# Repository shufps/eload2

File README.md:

> ⚠️ **Disclaimer / Status**
>
> This project is provided **AS IS**, **without any warranty** and **without any kind of support**.
> Use at your own risk — this is **high-current / high-power** hardware and can damage equipment or cause injury if used incorrectly.

# eload2 (Load v2)

A compact, over-engineered **multi-channel electronic load** for **low-voltage / high-current** testing — built because nothing affordable exists that does *0–1.5V @ ~100A* properly.

No display. Control via **USB** from a PC (Python), firmware on **STM32**.

## Why this exists

I needed a tool to:
- test **buck converters / VRMs** in the **0–1.5V** range at serious currents
- still be usable as a “normal” load at **12V** (e.g. for power supplies / battery projects)
- be stable, repeatable and boring (in the good sense)

Commercial options in this niche are either impractical or unreasonably expensive — so I built it.

## Highlights

- **4 independent channels**
- Designed for:
  - **0–1.5V** VRM / buck testing up to **~100A** total (depending on cooling & SOA)
  - **12V** testing (e.g. ~8–12A, depending on dissipation)
- Each channel has its own analog supply chain (low coupling, predictable behavior):
  - dedicated **9V LDO**
  - dedicated precision **reference** (REF3433)
  - dedicated **16-bit DAC**
  - dedicated **OPA2196** control loop
  - dedicated MOSFET “arm”
- MOSFETs: **BUK7S0R5-40HJ** (very low Rds(on), beefy SOA)
- Cooling: **SP3/TR4 CPU cooler** (tested in practice)
- High-current IO: **M4** power connections (aiming for ~80A per connector)
- PCB: **120 × 160 mm**, **4-layer**, 1oz/1oz
  (large copper, parallel layers, big via arrays; optional copper busbars)

## Status

- PCBs + stencil: ✅
- Parts: ✅ (BOM originally ~1.5 years old, most parts still available)
- Bring-up: ✅
- Verified load test: **12V @ 10A (120W) for ~15 min → ~55°C board temperature** (with the big cooler)

## Errata

- Current setting is a little bit off. For example 11.5A needs to be set for 10.0A current.

## Minimalistic Web UI

There is a minimalistic web UI.

It can be run using `streamlit`:
```bash
streamlit run eload_ui.py
```

## Documentation

https://www.mikrocontroller.net/topic/563073

## Repository structure (typical)

- `kicad/` – schematics, PCB, mechanical notes
- `firmware/` – STM32 firmware (Rust, Embassy)
- `python/` – PC tooling / scripts (Python)

## Quick start

### Firmware
- Build/flash using your usual STM32 + Rust toolchain.
- This project uses **Embassy** async tasks.

### Host control
- Connect the board via USB.
- Use the Python scripts to set:
  - per-channel DAC setpoints
  - PWM / fan / enable (depending on build)
  - read back telemetry (if enabled)

## Safety / Notes

This is a **high current** design.
- Use short, thick wiring for low-voltage/high-current tests.
- Treat every milliohm as a heater.
- Ensure solid cooling and stable mounting before sustained high power tests.
- If you don’t know what you’re doing: don’t connect this to expensive hardware.

## License

CERN-OHL-S: https://ohwr.org/cern_ohl_s_v2.pdf

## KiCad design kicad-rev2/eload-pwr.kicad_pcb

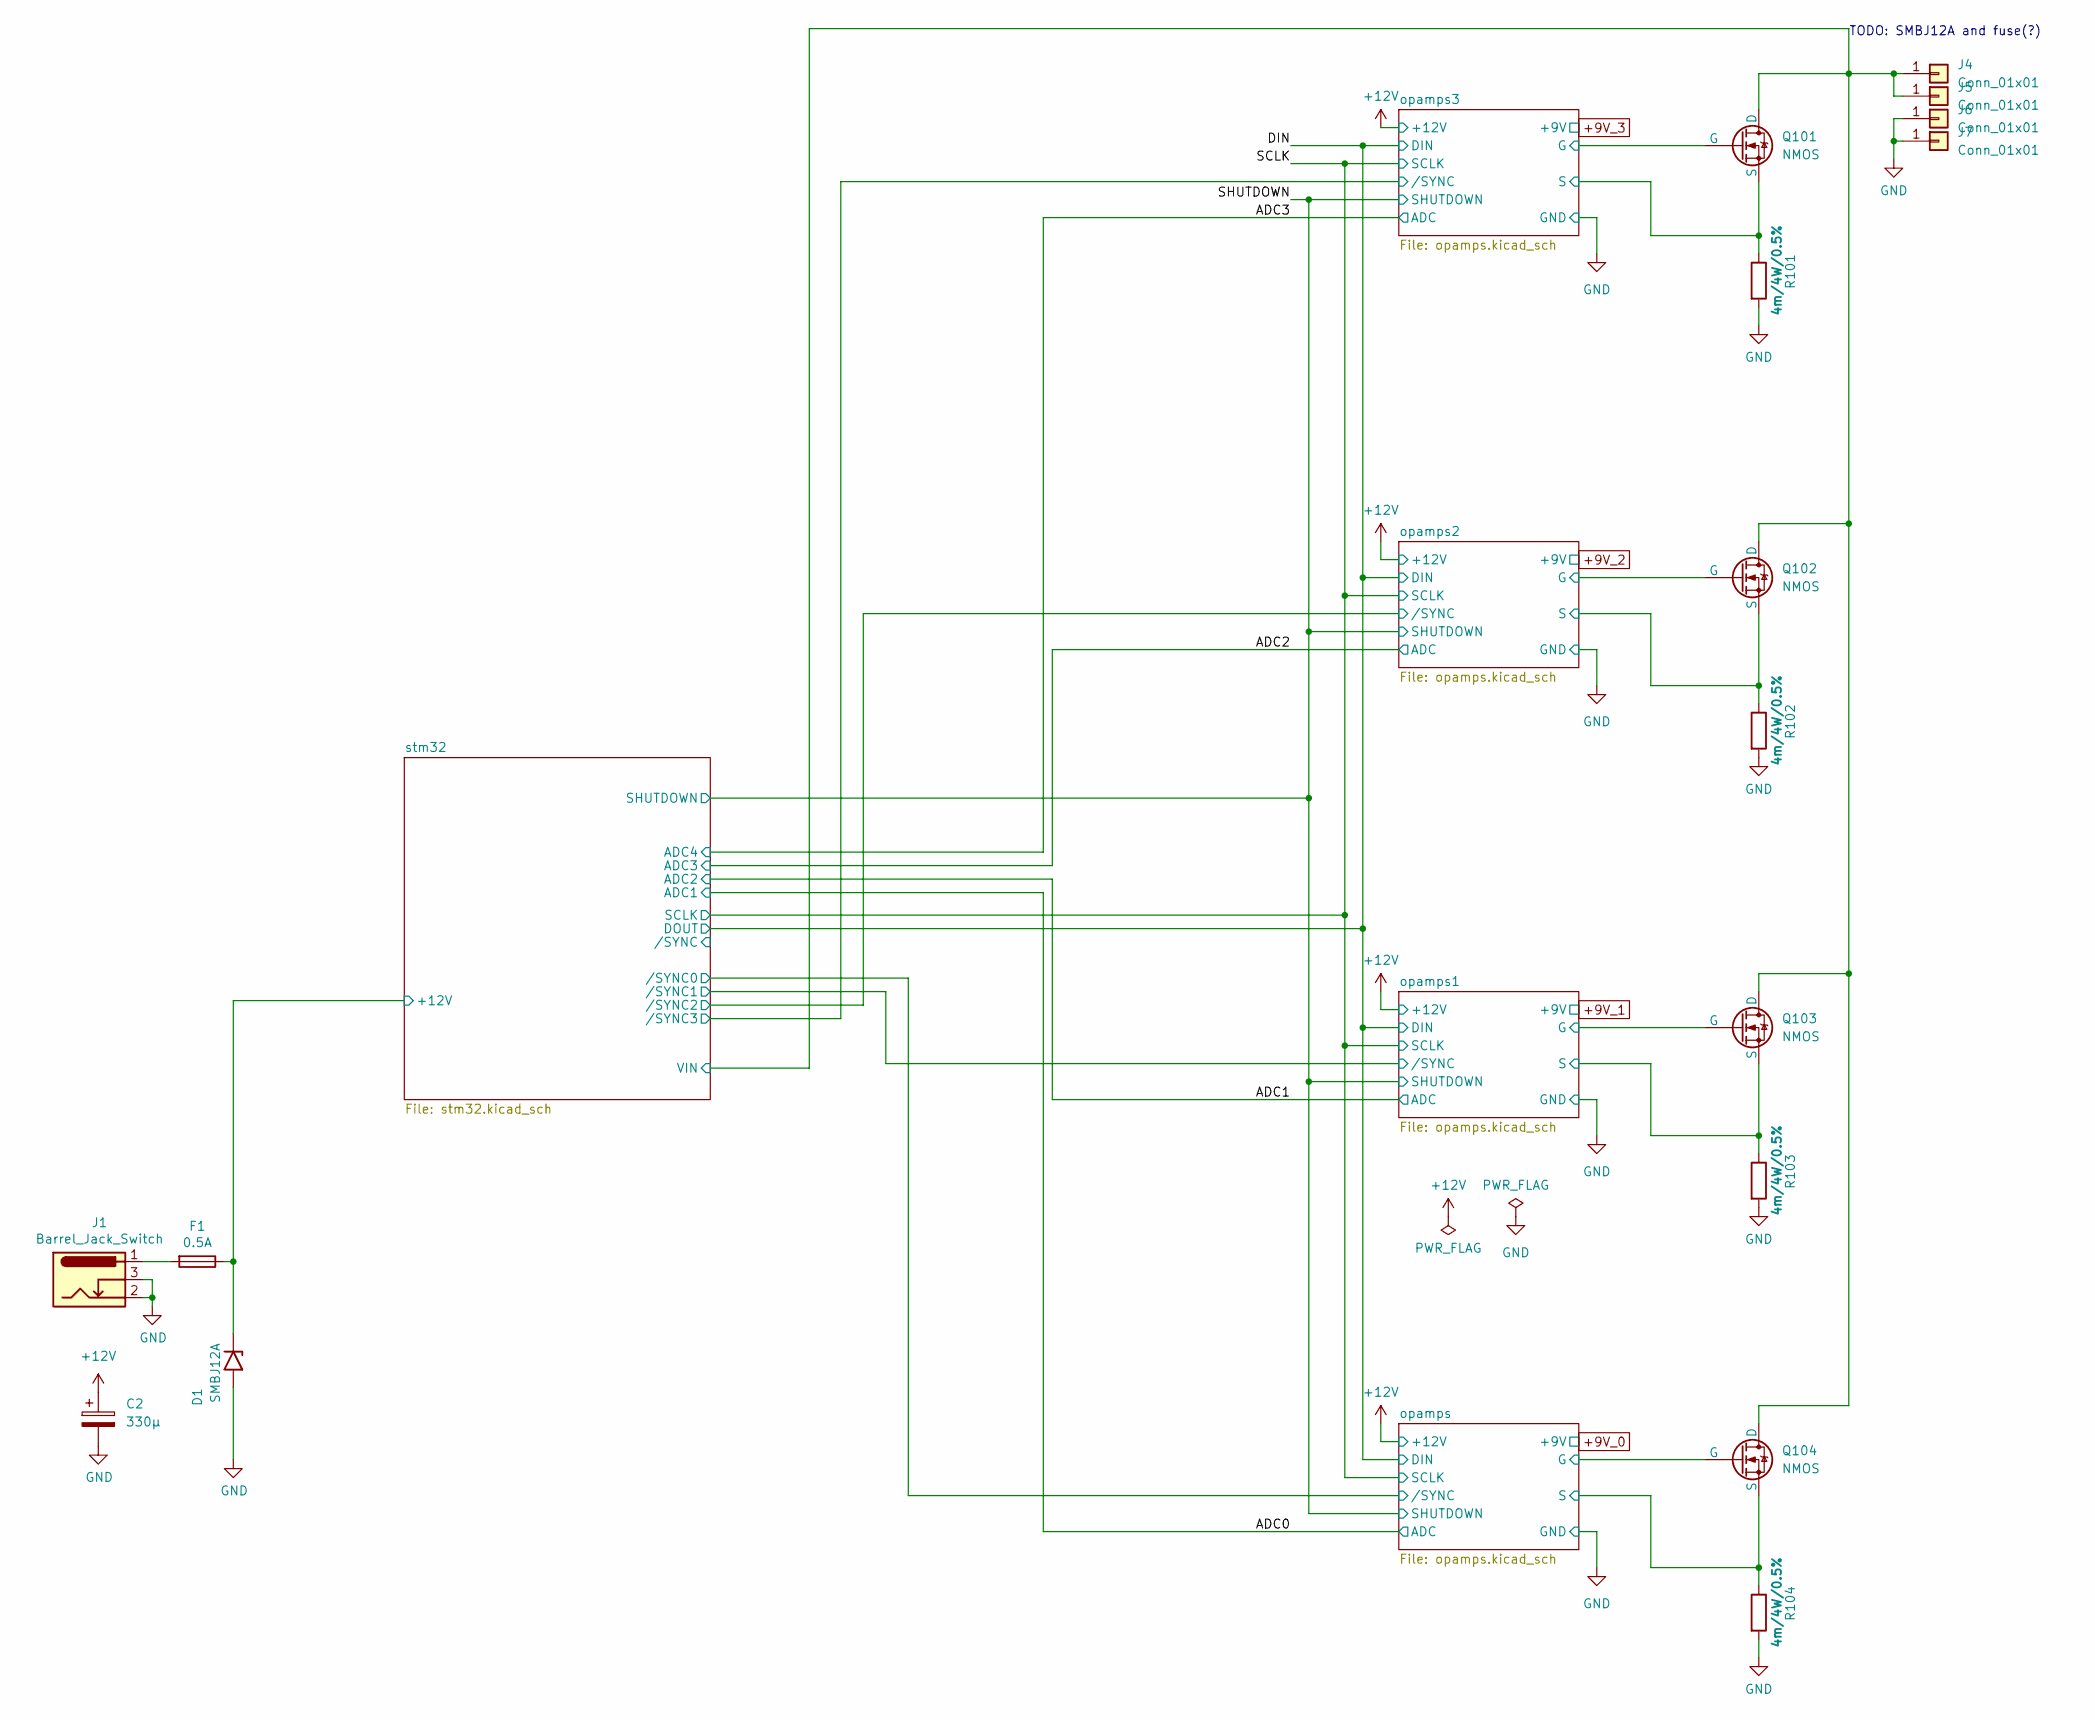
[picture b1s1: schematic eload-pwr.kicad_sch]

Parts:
C2: 330µ; CP_Elec_8x10
D1: SMBJ12A; D_SMB
F1: 0.5A; fuseholder_littlefuse_blok
J1: Barrel_Jack_Switch; BarrelJack_CUI_PJ-102AH_Horizontal
J4, J5, J6, J7: Conn_01x01; Wuerth_REDCUBE-THR_WP-THRBU_74650194_THR
Q101, Q102, Q103, Q104: NMOS; LFPAK88-SOT1235
R101, R102, R103, R104: 4m/4W/0.5%; R3920

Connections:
+12V: C2.1, D1.1 (A1), F1.1; also elsewhere on the board
/opamps1/G: Q103.G; also elsewhere on the board
/opamps1/S: Q103.S, R103.1; also elsewhere on the board
/opamps2/G: Q102.G; also elsewhere on the board
/opamps2/S: Q102.S, R102.1; also elsewhere on the board
/opamps3/G: Q101.G; also elsewhere on the board
/opamps3/S: Q101.S, R101.1; also elsewhere on the board
/opamps/G: Q104.G; also elsewhere on the board
/opamps/S: Q104.S, R104.1; also elsewhere on the board
/stm32/VIN: J4.1, J5.1, Q101.D, Q102.D, Q103.D, Q104.D; also elsewhere on the board
GND: C2.2, D1.2 (A2), J1.2, J1.3, J6.1, J7.1, R101.2, R102.2, R103.2, R104.2; also elsewhere on the board
unnamed: F1.2, J1.1

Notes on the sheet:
TODO: SMBJ12A and fuse(?)

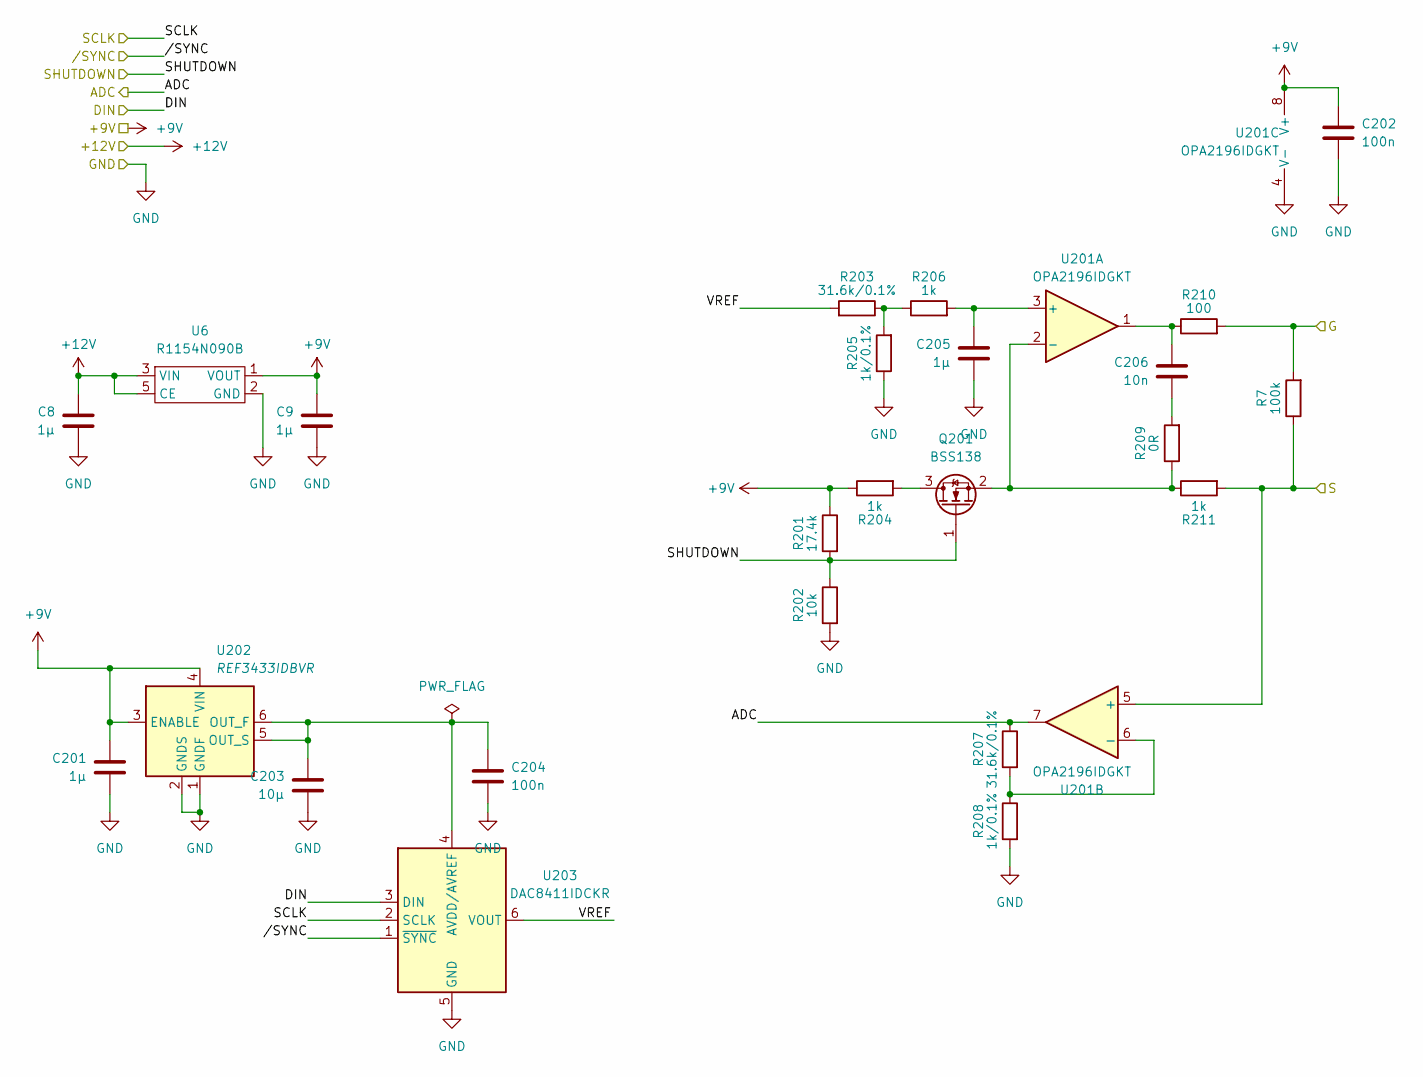
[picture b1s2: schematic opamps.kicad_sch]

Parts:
C8, C9, C201, C205: 1µ; C_0603_1608Metric
C202, C204: 100n; C_0603_1608Metric
C203: 10µ; C_0603_1608Metric
C206: 10n; C_0603_1608Metric
Q201: BSS138; SOT-23
R7: 100k; R_0603_1608Metric
R201: 17.4k; R_0603_1608Metric
R202: 10k; R_0603_1608Metric
R203, R207: 31.6k/0.1%; R_0603_1608Metric
R204, R206, R211: 1k; R_0603_1608Metric
R205, R208: 1k/0.1%; R_0603_1608Metric
R209: 0R; R_0603_1608Metric
R210: 100; R_0603_1608Metric
U6: R1154N090B; SOT-23-5
U201: OPA2196IDGKT; VSSOP-8_3.0x3.0mm_P0.65mm
U202: REF3433IDBVR; SOT-23-6
U203: DAC8411IDCKR; SOT-363_SC-70-6

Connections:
+9V_0: C9.1, C201.1, C202.1, R201.1, R204.1, U6.1 (VOUT), U201.8 (V+), U202.3 (ENABLE), U202.4 (VIN)
+12V: C8.1, U6.3 (VIN), U6.5 (CE); also elsewhere on the board
/ADC0: R207.1, U201.7; also elsewhere on the board
/DIN: U203.3 (DIN); also elsewhere on the board
/SCLK: U203.2 (SCLK); also elsewhere on the board
/SHUTDOWN: Q201.1 (G), R201.2, R202.1; also elsewhere on the board
/opamps/G: R7.2, R210.2; also elsewhere on the board
/opamps/S: R7.1, R211.2, U201.5 (+); also elsewhere on the board
/opamps/VREF: R203.2, U203.6 (VOUT)
/opamps//SYNC: U203.1 (~SYNC); also elsewhere on the board
GND: C8.2, C9.2, C201.2, C202.2, C203.2, C204.2, C205.2, R202.2, R205.1, R208.2, U6.2 (GND), U201.4 (V-), U202.1 (GNDF), U202.2 (GNDS), U203.5 (GND); also elsewhere on the board
unnamed: C206.1, R210.1, U201.1
unnamed: C206.2, R209.2
unnamed: Q201.3 (D), R204.2
unnamed: Q201.2 (S), R209.1, R211.1, U201.2 (-)
unnamed: R203.1, R205.2, R206.1
unnamed: C205.1, R206.2, U201.3 (+)
unnamed: R207.2, R208.1, U201.6 (-)
unnamed: C203.1, C204.1, U202.5 (OUT_S), U202.6 (OUT_F), U203.4 (AVDD/AVREF)

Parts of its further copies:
C12, C16, C17, C21, C22, C23, C301, C305, C401, C405, C501, C505: 1µ; C_0603_1608Metric
C302, C304, C402, C404, C502, C504: 100n; C_0603_1608Metric
C303, C403, C503: 10µ; C_0603_1608Metric
C306, C406, C506: 10n; C_0603_1608Metric
Q301, Q401, Q501: BSS138; SOT-23
R9, R10, R11: 100k; R_0603_1608Metric
R301, R401, R501: 17.4k; R_0603_1608Metric
R302, R402, R502: 10k; R_0603_1608Metric
R303, R307, R403, R407, R503, R507: 31.6k/0.1%; R_0603_1608Metric
R304, R306, R311, R404, R406, R411, R504, R506, R511: 1k; R_0603_1608Metric
R305, R308, R405, R408, R505, R508: 1k/0.1%; R_0603_1608Metric
R309, R409, R509: 0R; R_0603_1608Metric
R310, R410, R510: 100; R_0603_1608Metric
U7, U8, U9: R1154N090B; SOT-23-5
U301, U401, U501: OPA2196IDGKT; VSSOP-8_3.0x3.0mm_P0.65mm
U302, U402, U502: REF3433IDBVR; SOT-23-6
U303, U403, U503: DAC8411IDCKR; SOT-363_SC-70-6

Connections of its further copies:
+9V_1: C16.1, C301.1, C302.1, R301.1, R304.1, U7.1 (VOUT), U301.8 (V+), U302.3 (ENABLE), U302.4 (VIN)
+9V_2: C21.1, C401.1, C402.1, R401.1, R404.1, U8.1 (VOUT), U401.8 (V+), U402.3 (ENABLE), U402.4 (VIN)
+9V_3: C23.1, C501.1, C502.1, R501.1, R504.1, U9.1 (VOUT), U501.8 (V+), U502.3 (ENABLE), U502.4 (VIN)
+12V: C12.1, C17.1, C22.1, U7.3 (VIN), U7.5 (CE), U8.3 (VIN), U8.5 (CE), U9.3 (VIN), U9.5 (CE); also elsewhere on the board
/ADC1: R307.1, U301.7; also elsewhere on the board
/ADC2: R407.1, U401.7; also elsewhere on the board
/ADC3: R507.1, U501.7; also elsewhere on the board
/DIN: U303.3 (DIN), U403.3 (DIN), U503.3 (DIN); also elsewhere on the board
/SCLK: U303.2 (SCLK), U403.2 (SCLK), U503.2 (SCLK); also elsewhere on the board
/SHUTDOWN: Q301.1 (G), Q401.1 (G), Q501.1 (G), R301.2, R302.1, R401.2, R402.1, R501.2, R502.1; also elsewhere on the board
/opamps1/G: R9.2, R310.2; also elsewhere on the board
/opamps1/S: R9.1, R311.2, U301.5 (+); also elsewhere on the board
/opamps1/VREF: R303.2, U303.6 (VOUT)
/opamps1//SYNC: U303.1 (~SYNC); also elsewhere on the board
/opamps2/G: R10.2, R410.2; also elsewhere on the board
/opamps2/S: R10.1, R411.2, U401.5 (+); also elsewhere on the board
/opamps2/VREF: R403.2, U403.6 (VOUT)
/opamps2//SYNC: U403.1 (~SYNC); also elsewhere on the board
/opamps3/G: R11.2, R510.2; also elsewhere on the board
/opamps3/S: R11.1, R511.2, U501.5 (+); also elsewhere on the board
/opamps3/VREF: R503.2, U503.6 (VOUT)
/opamps3//SYNC: U503.1 (~SYNC); also elsewhere on the board
GND: C12.2, C16.2, C17.2, C21.2, C22.2, C23.2, C301.2, C302.2, C303.2, C304.2, C305.2, C401.2, C402.2, C403.2, C404.2, C405.2, C501.2, C502.2, C503.2, C504.2, C505.2, R302.2, R305.1, R308.2, R402.2, R405.1, R408.2, R502.2, R505.1, R508.2, U7.2 (GND), U8.2 (GND), U9.2 (GND), U301.4 (V-), U302.1 (GNDF), U302.2 (GNDS), U303.5 (GND), U401.4 (V-), U402.1 (GNDF), U402.2 (GNDS), U403.5 (GND), U501.4 (V-), U502.1 (GNDF), U502.2 (GNDS), U503.5 (GND); also elsewhere on the board
unnamed: C306.1, R310.1, U301.1
unnamed: C306.2, R309.2
unnamed: C406.1, R410.1, U401.1
unnamed: C406.2, R409.2
unnamed: C506.1, R510.1, U501.1
unnamed: C506.2, R509.2
unnamed: Q301.3 (D), R304.2
unnamed: Q301.2 (S), R309.1, R311.1, U301.2 (-)
unnamed: Q401.3 (D), R404.2
unnamed: Q401.2 (S), R409.1, R411.1, U401.2 (-)
unnamed: Q501.3 (D), R504.2
unnamed: Q501.2 (S), R509.1, R511.1, U501.2 (-)
unnamed: R303.1, R305.2, R306.1
unnamed: R403.1, R405.2, R406.1
unnamed: R503.1, R505.2, R506.1
unnamed: C305.1, R306.2, U301.3 (+)
unnamed: R307.2, R308.1, U301.6 (-)
unnamed: C303.1, C304.1, U302.5 (OUT_S), U302.6 (OUT_F), U303.4 (AVDD/AVREF)
unnamed: C405.1, R406.2, U401.3 (+)
unnamed: R407.2, R408.1, U401.6 (-)
unnamed: C403.1, C404.1, U402.5 (OUT_S), U402.6 (OUT_F), U403.4 (AVDD/AVREF)
unnamed: C505.1, R506.2, U501.3 (+)
unnamed: R507.2, R508.1, U501.6 (-)
unnamed: C503.1, C504.1, U502.5 (OUT_S), U502.6 (OUT_F), U503.4 (AVDD/AVREF)

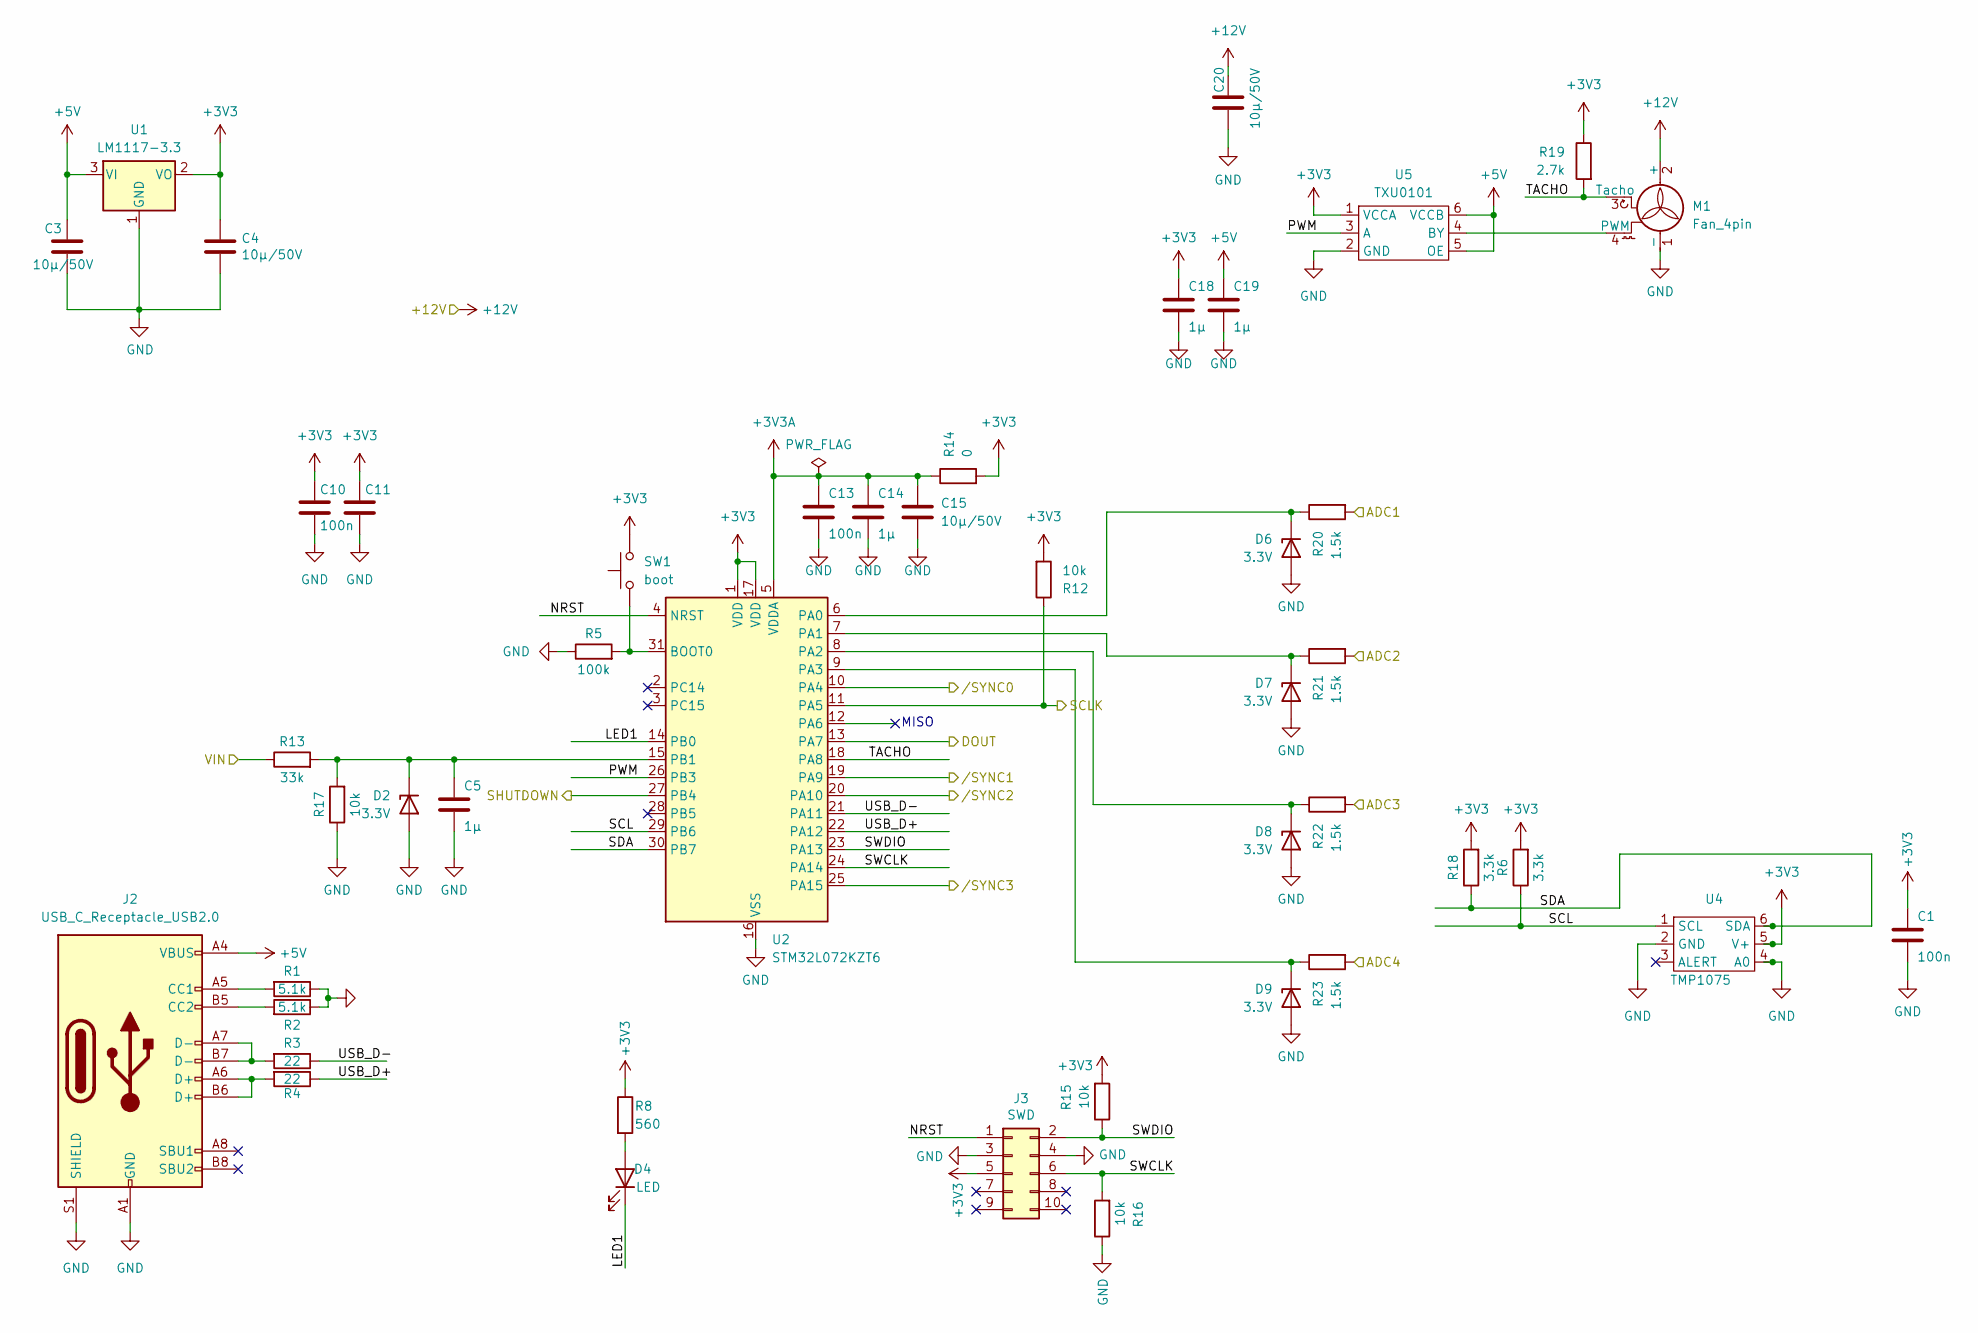
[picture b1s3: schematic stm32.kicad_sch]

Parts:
C1: 100n; C_0603_1608Metric
C3, C4, C15, C20: 10µ/50V; C_1206_3216Metric
C5, C14, C18, C19: 1µ; C_0805_2012Metric
C10, C11, C13: 100n; C_0805_2012Metric
D2, D6, D7, D8, D9: 3.3V; D_MiniMELF
D4: LED; LED_1206_3216Metric
J2: USB_C_Receptacle_USB2.0; USB_C_Receptacle_GCT_USB4105-xx-A_16P_TopMnt_Horizontal
J3: SWD; PinHeader_IDC_2x05_P1.27mm_Vertical_SMD
M1: Fan_4pin; FanPinHeader_1x04_P2.54mm_Vertical
R1, R2: 5.1k; R_0805_2012Metric
R3, R4: 22; R_0805_2012Metric
R5: 100k; R_0805_2012Metric
R6, R18: 3.3k; R_0805_2012Metric
R8: 560; R_0805_2012Metric
R12, R15, R16, R17: 10k; R_0805_2012Metric
R13: 33k; R_0805_2012Metric
R14: 0; R_0805_2012Metric
R19: 2.7k; R_0805_2012Metric
R20, R21, R22, R23: 1.5k; R_0805_2012Metric
SW1: boot; SW_Push_1P1T_NO_CK_KMR2
U1: LM1117-3.3; SOT-223-3_TabPin2
U2: STM32L072KZT6; LQFP-32_7x7mm_P0.8mm
U4: TMP1075; TMP1075-DRL
U5: TXU0101; SOT-363_SC-70-6

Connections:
+3V3: C1.1, C4.1, C10.1, C11.1, C18.1, J3.5, R6.2, R8.1, R12.2, R14.2, R15.2, R18.2, R19.1, SW1.2, U1.2 (VO), U2.1 (VDD), U2.17 (VDD), U4.5 (V+), U5.1 (VCCA)
+3V3A: C13.1, C14.1, C15.1, R14.1, U2.5 (VDDA)
+5V: C3.1, C19.1, J2.A4 (VBUS), J2.A9 (VBUS), J2.B4 (VBUS), J2.B9 (VBUS), U1.3 (VI), U5.5 (OE), U5.6 (VCCB)
+12V: C20.1, M1.2 (+); also elsewhere on the board
/ADC0: R20.2; also elsewhere on the board
/ADC1: R21.2; also elsewhere on the board
/ADC2: R22.2; also elsewhere on the board
/ADC3: R23.2; also elsewhere on the board
/DIN: U2.13 (PA7); also elsewhere on the board
/SCLK: R12.1, U2.11 (PA5); also elsewhere on the board
/SHUTDOWN: U2.27 (PB4); also elsewhere on the board
/opamps1//SYNC: U2.19 (PA9); also elsewhere on the board
/opamps2//SYNC: U2.20 (PA10); also elsewhere on the board
/opamps3//SYNC: U2.25 (PA15); also elsewhere on the board
/opamps//SYNC: U2.10 (PA4); also elsewhere on the board
/stm32/LED1: D4.1 (K), U2.14 (PB0)
/stm32/NRST: J3.1, U2.4 (NRST)
/stm32/PWM: U2.26 (PB3), U5.3 (A)
/stm32/SCL: R6.1, U2.29 (PB6), U4.1 (SCL)
/stm32/SDA: R18.1, U2.30 (PB7), U4.6 (SDA)
/stm32/SWCLK: J3.6, R16.2, U2.24 (PA14)
/stm32/SWDIO: J3.2, R15.1, U2.23 (PA13)
/stm32/TACHO: M1.3 (Tacho), R19.2, U2.18 (PA8)
/stm32/USB_D+: R4.1, U2.22 (PA12)
/stm32/USB_D-: R3.1, U2.21 (PA11)
/stm32/VIN: R13.1; also elsewhere on the board
GND: C1.2, C3.2, C4.2, C5.2, C10.2, C11.2, C13.2, C14.2, C15.2, C18.2, C19.2, C20.2, D2.2 (A), D6.2 (A), D7.2 (A), D8.2 (A), D9.2 (A), J2.A1 (GND), J2.A12 (GND), J2.B1 (GND), J2.B12 (GND), J2.S1 (SHIELD), J3.3, J3.4, M1.1 (-), R1.1, R2.1, R5.1, R16.1, R17.1, U1.1 (GND), U2.16 (VSS), U2.32 (VSS), U4.2 (GND), U4.4 (A0), U5.2 (GND); also elsewhere on the board
unnamed: C5.1, D2.1 (K), R13.2, R17.2, U2.15 (PB1)
unnamed: D4.2 (A), R8.2
unnamed: D6.1 (K), R20.1, U2.6 (PA0)
unnamed: D7.1 (K), R21.1, U2.7 (PA1)
unnamed: D8.1 (K), R22.1, U2.8 (PA2)
unnamed: D9.1 (K), R23.1, U2.9 (PA3)
unnamed: J2.A5 (CC1), R1.2
unnamed: J2.B5 (CC2), R2.2
unnamed: J2.A6 (D+), J2.B6 (D+), R4.2
unnamed: J2.A7 (D-), J2.B7 (D-), R3.2
unnamed: M1.4 (PWM), U5.4 (BY)
unnamed: R5.2, SW1.1, U2.31 (BOOT0)

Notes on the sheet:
MISO

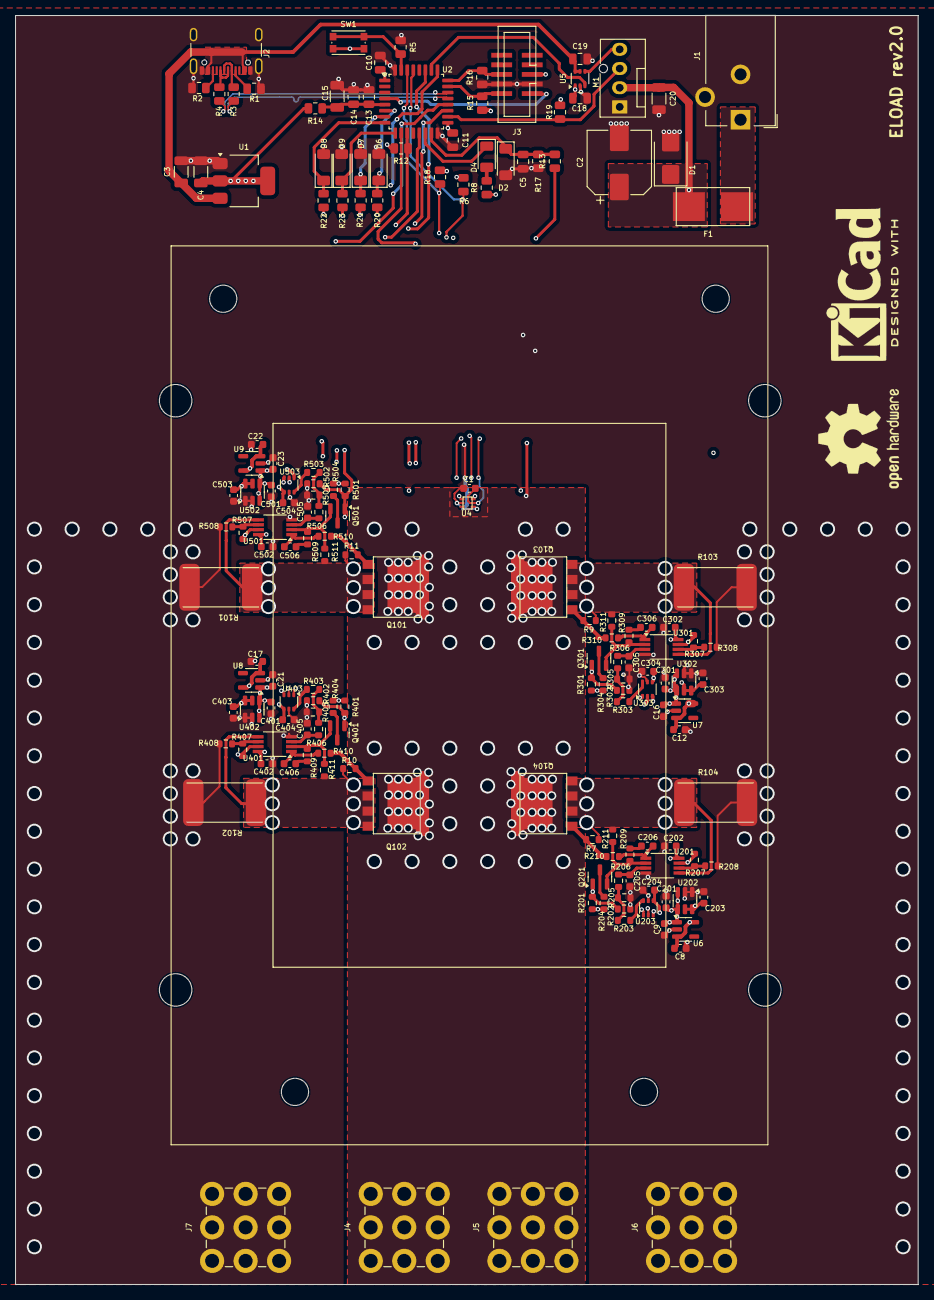
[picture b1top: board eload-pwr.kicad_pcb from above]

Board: 4 copper layers, 119.5 x 168.0 mm, 161 parts (0 on the bottom side), 88 nets.

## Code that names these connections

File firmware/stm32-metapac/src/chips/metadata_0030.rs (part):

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        ),
        pins: &[
            PeripheralPin {
                pin: "PA0",
                signal: "IN0",
                af: None,
            },
            PeripheralPin {
                pin: "PA1",
                signal: "IN1",
                af: None,
            },
            PeripheralPin {
                pin: "PA2",
                signal: "IN2",
                af: None,
            },
            PeripheralPin {
                pin: "PA3",
                signal: "IN3",
                af: None,
            },
            PeripheralPin {
                pin: "PA4",
                signal: "IN4",
                af: None,
            },
            PeripheralPin {
                pin: "PA5",
                signal: "IN5",
                af: None,
            },
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                af: None,
            },
            PeripheralPin {
                pin: "PA7",
                signal: "IN7",
                af: None,
            },
            PeripheralPin {
                pin: "PB0",
                signal: "IN8",
                af: None,
            },
            PeripheralPin {
                pin: "PB1",
                signal: "IN9",
                af: None,
            },
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        ),
        pins: &[
            PeripheralPin {
                pin: "PA8",
                signal: "SYNC",
                af: Some(
                    4,
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        ),
        pins: &[
            PeripheralPin {
                pin: "PA10",
                signal: "SDA",
                af: Some(
                    4,
                ),
            },
            PeripheralPin {
                pin: "PA11",
                signal: "SCL",
                af: Some(
                    5,
                ),
            },
            PeripheralPin {
                pin: "PA12",
                signal: "SDA",
                af: Some(
                    5,
                ),
            },
            PeripheralPin {
                pin: "PA9",
                signal: "SCL",
                af: Some(
                    4,
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                ),
            },
            PeripheralPin {
                pin: "PB6",
                signal: "SCL",
                af: Some(
                    1,
                ),
            },
            PeripheralPin {
                pin: "PB7",
                signal: "SDA",
                af: Some(
                    1,
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        rcc: None,
        pins: &[
            PeripheralPin {
                pin: "PA8",
                signal: "MCO",
                af: Some(
                    0,
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        rcc: None,
        pins: &[
            PeripheralPin {
                pin: "PA0",
                signal: "TAMP2",
                af: None,
            },
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        ),
        pins: &[
            PeripheralPin {
                pin: "PA15",
                signal: "I2S_WS",
                af: Some(
                    0,
                ),
            },
            PeripheralPin {
                pin: "PA15",
                signal: "NSS",
                af: Some(
                    0,
                ),
            },
            PeripheralPin {
                pin: "PA4",
                signal: "I2S_WS",
                af: Some(
                    0,
                ),
            },
            PeripheralPin {
                pin: "PA4",
                signal: "NSS",
                af: Some(
                    0,
                ),
            },
            PeripheralPin {
                pin: "PA5",
                signal: "I2S_CK",
                af: Some(
                    0,
                ),
            },
            PeripheralPin {
                pin: "PA5",
                signal: "SCK",
                af: Some(
                    0,
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                ),
            },
            PeripheralPin {
                pin: "PA7",
                signal: "I2S_SD",
                af: Some(
                    0,
                ),
            },
            PeripheralPin {
                pin: "PA7",
                signal: "MOSI",
                af: Some(
                    0,
                ),
            },
            PeripheralPin {
                pin: "PB3",
                signal: "I2S_CK",
                af: Some(
                    0,
                ),
            },
            PeripheralPin {
                pin: "PB3",
                signal: "SCK",
                af: Some(
                    0,
                ),
            },
            PeripheralPin {
                pin: "PB4",
                signal: "I2S_MCK",
                af: Some(
                    0,
                ),
            },
            PeripheralPin {
                pin: "PB4",
                signal: "MISO",
                af: Some(
                    0,
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        ),
        pins: &[
            PeripheralPin {
                pin: "PA10",
                signal: "CH3",
                af: Some(
                    2,
                ),
            },
            PeripheralPin {
                pin: "PA11",
                signal: "CH4",
                af: Some(
                    2,
                ),
            },
            PeripheralPin {
                pin: "PA12",
                signal: "ETR",
                af: Some(
                    2,
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                ),
            },
            PeripheralPin {
                pin: "PA7",
                signal: "CH1N",
                af: Some(
                    2,
                ),
            },
            PeripheralPin {
                pin: "PA8",
                signal: "CH1",
                af: Some(
                    2,
                ),
            },
            PeripheralPin {
                pin: "PA9",
                signal: "CH2",
                af: Some(
                    2,
                ),
            },
            PeripheralPin {
                pin: "PB0",
                signal: "CH2N",
                af: Some(
                    2,
                ),
            },
            PeripheralPin {
                pin: "PB1",
                signal: "CH3N",
                af: Some(
                    2,
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        ),
        pins: &[
            PeripheralPin {
                pin: "PA4",
                signal: "CH1",
                af: Some(
                    4,
                ),
            },
            PeripheralPin {
                pin: "PA7",
                signal: "CH1",
                af: Some(
                    4,
                ),
            },
            PeripheralPin {
                pin: "PB1",
                signal: "CH1",
                af: Some(
                    0,
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                ),
            },
            PeripheralPin {
                pin: "PB6",
                signal: "CH1N",
                af: Some(
                    2,
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        ),
        pins: &[
            PeripheralPin {
                pin: "PA10",
                signal: "BKIN",
                af: Some(
                    0,
                ),
            },
            PeripheralPin {
                pin: "PA7",
                signal: "CH1",
                af: Some(
                    5,
                ),
            },
            PeripheralPin {
                pin: "PB4",
                signal: "BKIN",
                af: Some(
                    5,
                ),
            },
            PeripheralPin {
                pin: "PB7",
                signal: "CH1N",
                af: Some(
                    2,
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        ),
        pins: &[
            PeripheralPin {
                pin: "PA0",
                signal: "CH1",
                af: Some(
                    2,
                ),
            },
            PeripheralPin {
                pin: "PA0",
                signal: "ETR",
                af: Some(
                    2,
                ),
            },
            PeripheralPin {
                pin: "PA1",
                signal: "CH2",
                af: Some(
                    2,
                ),
            },
            PeripheralPin {
                pin: "PA15",
                signal: "CH1",
                af: Some(
                    2,
                ),
            },
            PeripheralPin {
                pin: "PA15",
                signal: "ETR",
                af: Some(
                    2,
                ),
            },
            PeripheralPin {
                pin: "PA2",
                signal: "CH3",
                af: Some(
                    2,
                ),
            },
            PeripheralPin {
                pin: "PA3",
                signal: "CH4",
                af: Some(
                    2,
                ),
            },
            PeripheralPin {
                pin: "PA5",
                signal: "CH1",
                af: Some(
                    2,
                ),
            },
            PeripheralPin {
                pin: "PA5",
                signal: "ETR",
                af: Some(
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
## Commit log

2025-12-19 restructured directories
2025-12-19 set 22R to 0R (fix for adc)
2025-12-19 Remove credits section from README
2025-12-19 calculate power
2025-12-19 Update README with errata and web UI details
    Added errata and minimalistic web UI sections to README.
2025-12-26 correct ampere setting by 13.36%
